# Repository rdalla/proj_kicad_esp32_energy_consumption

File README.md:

# ESP32 ENERGY MONITORING MODULE

##MAIN COMPONENTS:
- ESP-WROOM-32 (ESP32 WIFI MODULE)
- SCT-013 50A/1V (CURRENT SENSOR 50A - NOT INVASIVE)

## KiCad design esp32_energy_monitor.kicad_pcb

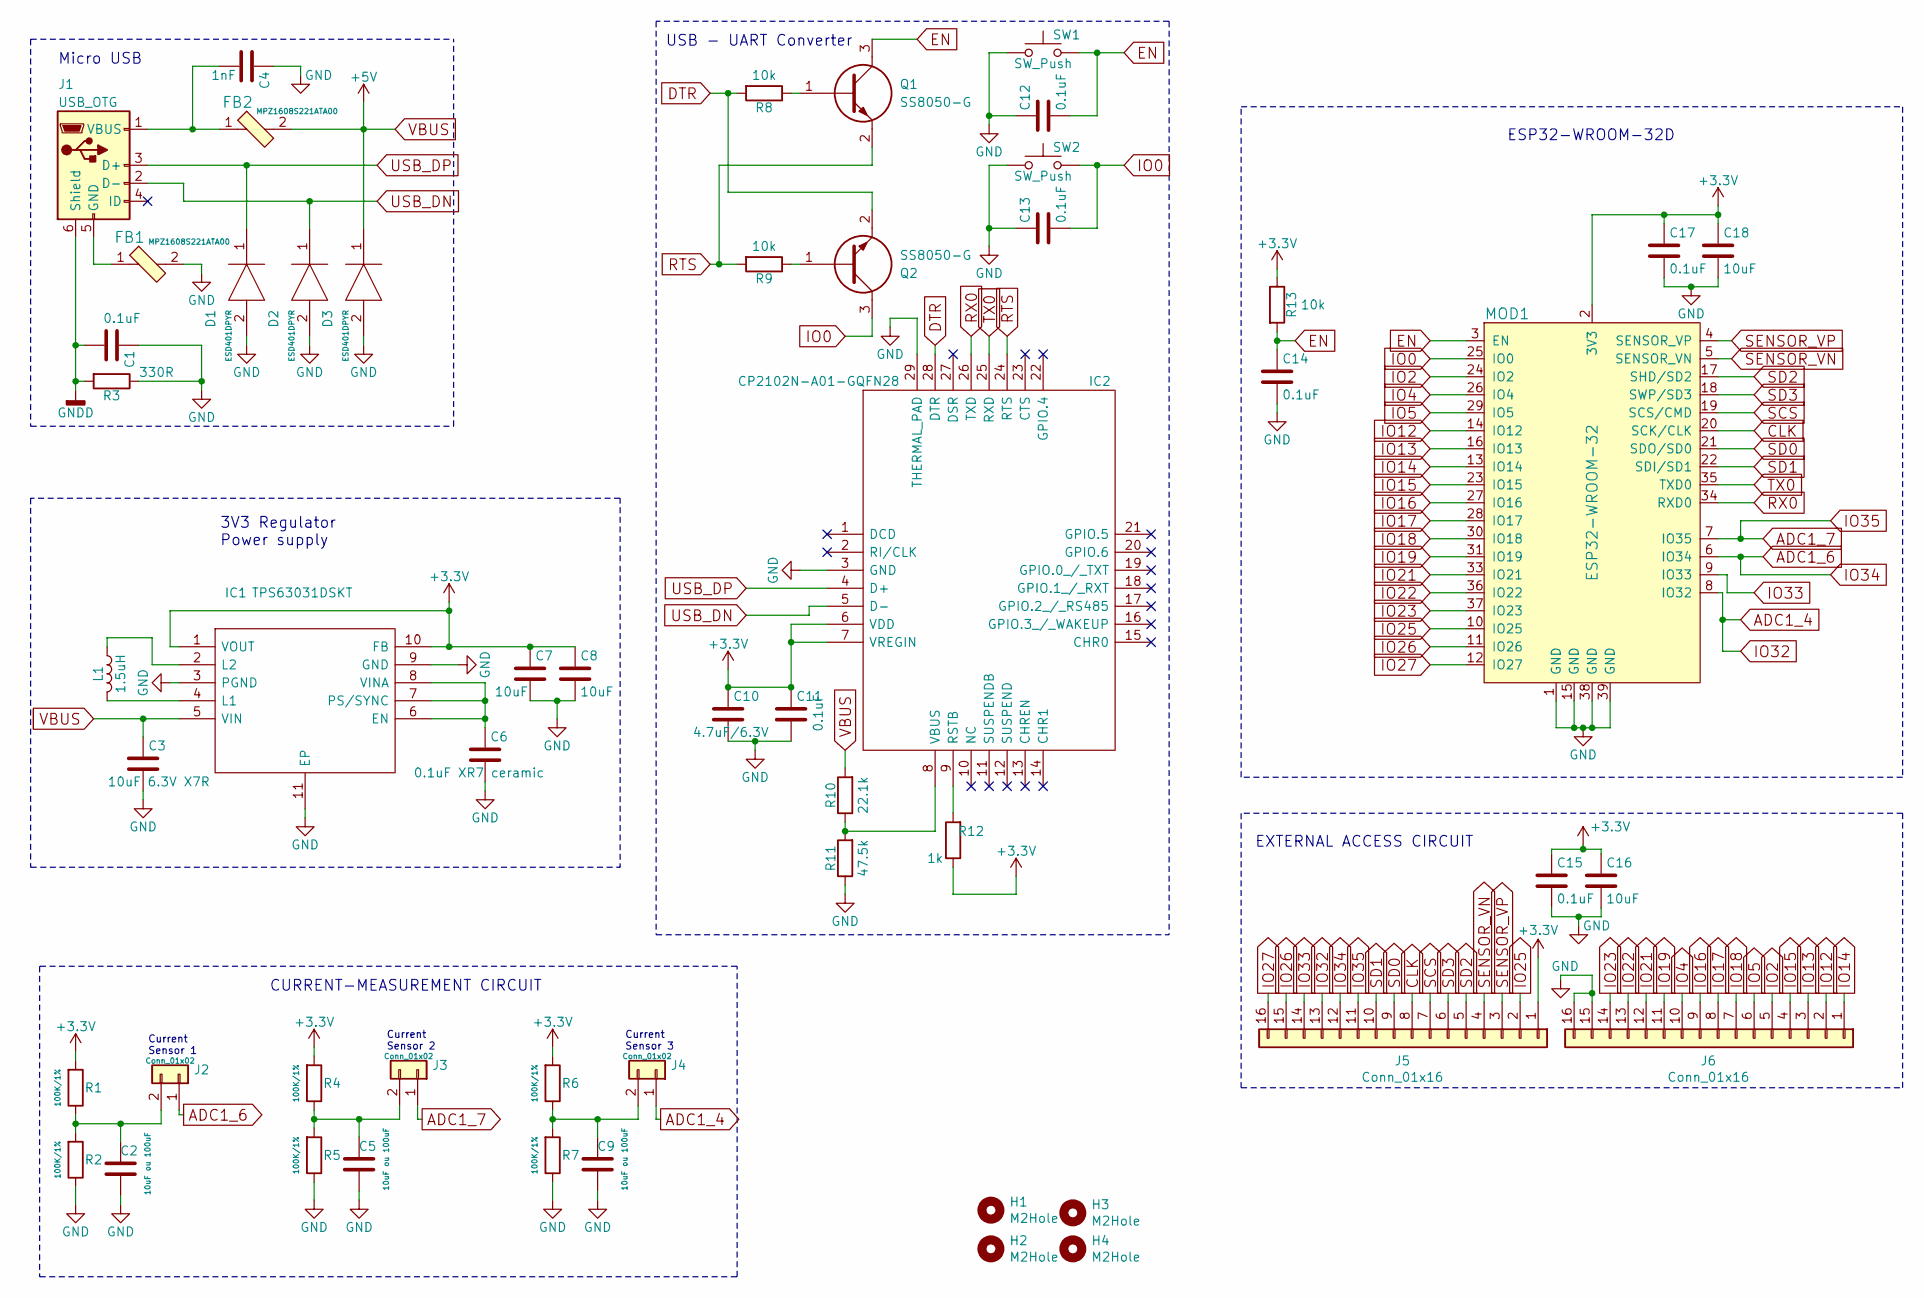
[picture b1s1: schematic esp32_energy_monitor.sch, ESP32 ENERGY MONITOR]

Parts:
C1, C11, C12, C13, C14, C15, C17: 0.1uF; C_0603
C2, C5, C9: 10uF ou 100uF; C_0603
C3: 10uF 6.3V X7R; C_0603
C4: 1nF; C_0603
C6: 0.1uF XR7 ceramic; C_0603
C7, C8, C16, C18: 10uF; C_0603
C10: 4.7uF/6.3V; C_0603
D1, D2, D3: ESD401DPYR; DPY_R-PX1SON-N2_; Manufacturer_Part_Number ESD401DPYR; Mouser Part Number 595-ESD401DPYR
FB1, FB2: MPZ1608S221ATA00; 0603; MPN MPZ1608S221ATA00; Digi-Key_PN 445-1565-1-ND
H1, H2, H3, H4: M2Hole; MountingHole_2.2mm_M2_DIN965
IC1: TPS63031DSKT; SON50P250X250X80-11N-D; Mouser Part Number 595-TPS63031DSKT
IC2: CP2102N-A01-GQFN28; QFN50P500X500X80-29N-D; Mouser Part Number 634-CP2102NA01GQFN28
J1: USB_OTG; USB_Micro_B_Female_1050170001
J2, J3, J4: Conn_01x02; Pin_Header_Straight_1x02_Pitch2.54mm
J5, J6: Conn_01x16; PinHeader_1x16_P2.54mm_Vertical
L1: 1.5uH; INDC3030X120N
MOD1: ESP32-WROOM-32; ESP32WROOM32D; MPN ESP32-WROOM-32; Digi-Key_PN 1904-1010-1-ND
Q1, Q2: SS8050-G; SOT95P240X115-3N; Mouser Part Number 750-SS8050-G
R1, R2, R4, R5, R6, R7: 100K/1%; R_0603
R3: 330R; R_0603
R8, R9, R13: 10k; R_0603
R10: 22.1k; R_0603
R11: 47.5k; R_0603
R12: 1k; R_0603
SW1, SW2: SW_Push; SW_SPST_B3U-1000P

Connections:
+3V3: C7.1, C8.1, C10.1, C11.1, C15.1, C16.1, C17.1, C18.1, IC1.1 (VOUT), IC1.10 (FB), IC2.6 (VDD), IC2.7 (VREGIN), J5.1, MOD1.2 (3V3), R1.2, R4.2, R6.2, R12.1, R13.1
ADC1_4: J4.1, J5.13, MOD1.8 (IO32)
ADC1_6: J2.1, J5.12, MOD1.6 (IO34)
ADC1_7: J3.1, J5.11, MOD1.7 (IO35)
CLK: J5.8, MOD1.20 (SCK/CLK)
DTR: IC2.28 (DTR), Q2.2, R8.2
EN: C12.2, C14.1, MOD1.3 (EN), Q1.3, R13.2, SW1.2
GND: C1.1, C2.2, C3.2, C4.1, C5.2, C6.2, C7.2, C8.2, C9.2, C10.2, C11.2, C12.1, C13.1, C14.2, C15.2, C16.2, C17.2, C18.2, D1.2, D2.2, D3.2, FB1.2, IC1.3 (PGND), IC1.9 (GND), IC1.11 (EP), IC2.3 (GND), IC2.29 (THERMAL_PAD), J6.15, J6.16, MOD1.1 (GND), MOD1.15 (GND), MOD1.38 (GND), MOD1.39 (GND), R2.1, R3.1, R5.1, R7.1, R11.1, SW1.1, SW2.1
GNDD: C1.2, J1.6 (Shield), J1.SH, R3.2
IO0: C13.2, MOD1.25 (IO0), Q2.3, SW2.2
IO2: J6.5, MOD1.24 (IO2)
IO4: J6.10, MOD1.26 (IO4)
IO5: J6.6, MOD1.29 (IO5)
IO12: J6.2, MOD1.14 (IO12)
IO13: J6.3, MOD1.16 (IO13)
IO14: J6.1, MOD1.13 (IO14)
IO15: J6.4, MOD1.23 (IO15)
IO16: J6.9, MOD1.27 (IO16)
IO17: J6.8, MOD1.28 (IO17)
IO18: J6.7, MOD1.30 (IO18)
IO19: J6.11, MOD1.31 (IO19)
IO21: J6.12, MOD1.33 (IO21)
IO22: J6.13, MOD1.36 (IO22)
IO23: J6.14, MOD1.37 (IO23)
IO25: J5.2, MOD1.10 (IO25)
IO26: J5.15, MOD1.11 (IO26)
IO27: J5.16, MOD1.12 (IO27)
IO33: J5.14, MOD1.9 (IO33)
unnamed: C2.1, J2.2, R1.1, R2.2
unnamed: C4.2, FB2.1, J1.1 (VBUS)
unnamed: C5.1, J3.2, R4.1, R5.2
unnamed: C6.1, IC1.6 (EN), IC1.7 (PS/SYNC), IC1.8 (VINA)
unnamed: C9.1, J4.2, R6.1, R7.2
unnamed: FB1.1, J1.5 (GND)
unnamed: IC1.2 (L2), L1.1
unnamed: IC1.4 (L1), L1.2
unnamed: IC2.8 (VBUS), R10.1, R11.2
unnamed: IC2.9 (RSTB), R12.2
unnamed: Q1.1, R8.1
unnamed: Q2.1, R9.1
RTS: IC2.24 (RTS), Q1.2, R9.2
RX0: IC2.26 (TXD), MOD1.34 (RXD0)
SCS: J5.7, MOD1.19 (SCS/CMD)
SD0: J5.9, MOD1.21 (SDO/SD0)
SD1: J5.10, MOD1.22 (SDI/SD1)
SD2: J5.5, MOD1.17 (SHD/SD2)
SD3: J5.6, MOD1.18 (SWP/SD3)
SENSOR_VN: J5.4, MOD1.5 (SENSOR_VN)
SENSOR_VP: J5.3, MOD1.4 (SENSOR_VP)
TX0: IC2.25 (RXD), MOD1.35 (TXD0)
USB_DN: D2.1, IC2.5 (D-), J1.2 (D-)
USB_DP: D1.1, IC2.4 (D+), J1.3 (D+)
VBUS: C3.1, D3.1, FB2.2, IC1.5 (VIN), R10.2

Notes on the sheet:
Micro USB
3V3 Regulator Power supply
USB - UART Converter
Current Sensor 2
Current Sensor 1
Current Sensor 3
ESP32-WROOM-32D
CURRENT-MEASUREMENT CIRCUIT
EXTERNAL ACCESS CIRCUIT

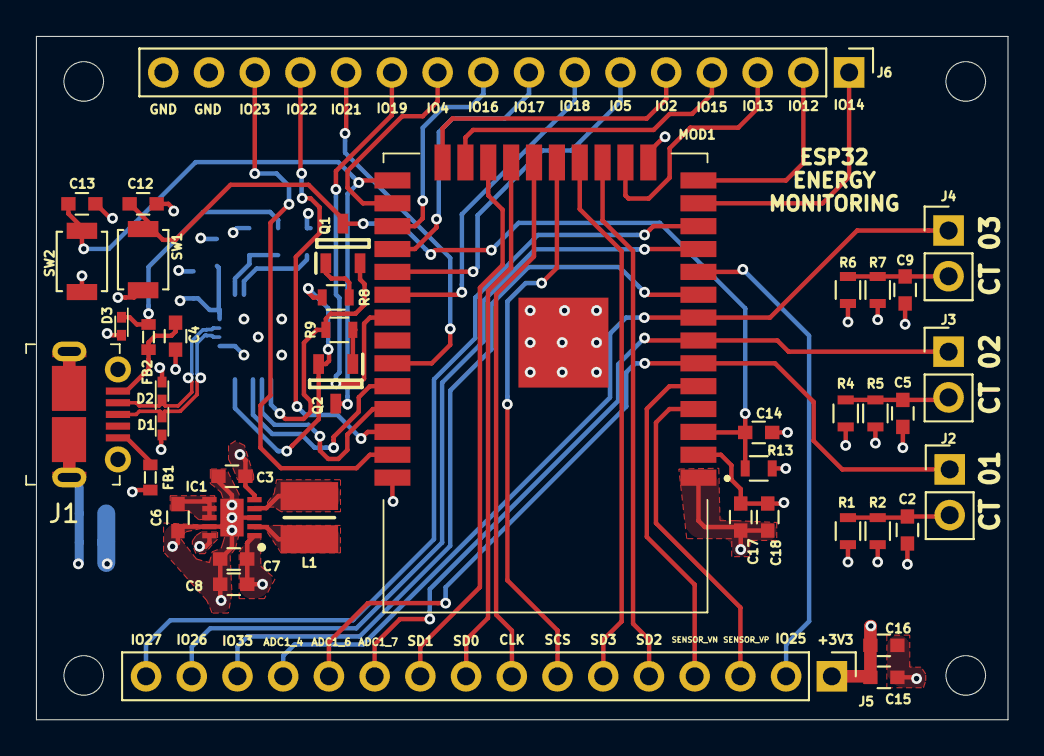
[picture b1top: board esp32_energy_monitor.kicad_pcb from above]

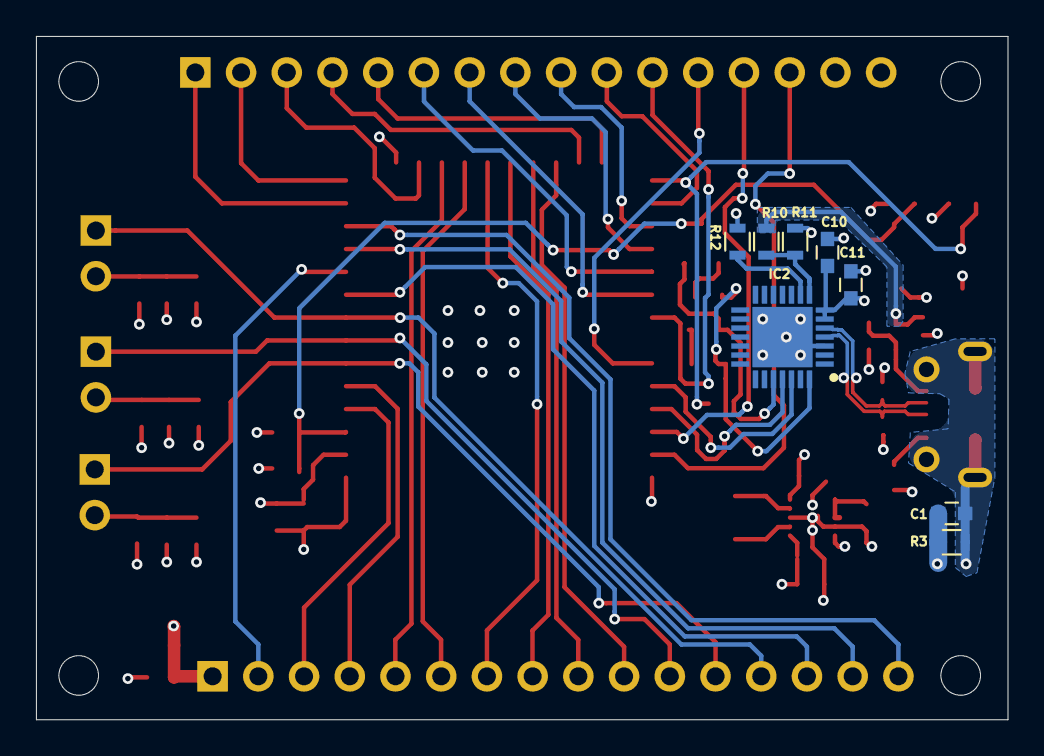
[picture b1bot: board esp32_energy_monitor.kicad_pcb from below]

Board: 4 copper layers, 54.0 x 38.0 mm, 54 parts (8 on the bottom side), 53 nets.

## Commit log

2020-06-22 Added the first sketch of the schematic. The developed circuits are: - 3V3 Power Supply - TPS63031DSKT - Micro USB Circuit (TVS and filters) - USB to UART Converter - CP2102N - ESP32 basic circuit (b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
2020-06-23 Added the ADS1115IDGSR ADC circuit with the signal conditioning to current sensor SCT-013-020 (30A).
2020-07-27 Schematic: Removed ADS1115 circuit. Removed Battery Protection circuit. Removed Battery Charger circuit. Removed Wake Up Button. Added external access circuit. Added three current measure circuit. It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
    Layout:
    Added the footprint library of the project.
    Changed the ESP32 footprint.
    Changed the position of the power supply circuit. (near of USB connector)
    3D View:
    Added ESP32 3D format step.
2020-07-27 Included all the footprints of the project on the same library "proj_kicad_esp32_energy_consumption".
2020-08-01 Added to the library of the project the pin header footprint.
    Schematic:
    Changed the position of the pins on J5 and J6 to layout better on the board.
    Layout:
    Added all the route tracks of the J5 and J6 connectors
    Added 3V3 Power Plane and the VBUS Power Plane
    Changed the format of the Ground Plane.
2020-08-01 Added to the library of the project the pin header footprint. Added the first version of the Bill of the Materials (BoM) of the board. Added the StackUp of the board.
    Schematic:
    Changed the position of the pins on J5 and J6 to layout better on the board.
    Layout:
    Added all the route tracks of the J5 and J6 connectors
    Added 3V3 Power Plane and the VBUS Power Plane
    Changed the format of the Ground Plane.
2020-08-23 Improved the layout of the J5 and J6 to expose all the pins of the ESP32 module.
    Added the Final version of Bill of Materials (BoM).
    Added all the gerber files.
2020-08-23 Fixed issue in the file kicad_pcb.
2020-08-23 Fixed the file kicad_pcb.
